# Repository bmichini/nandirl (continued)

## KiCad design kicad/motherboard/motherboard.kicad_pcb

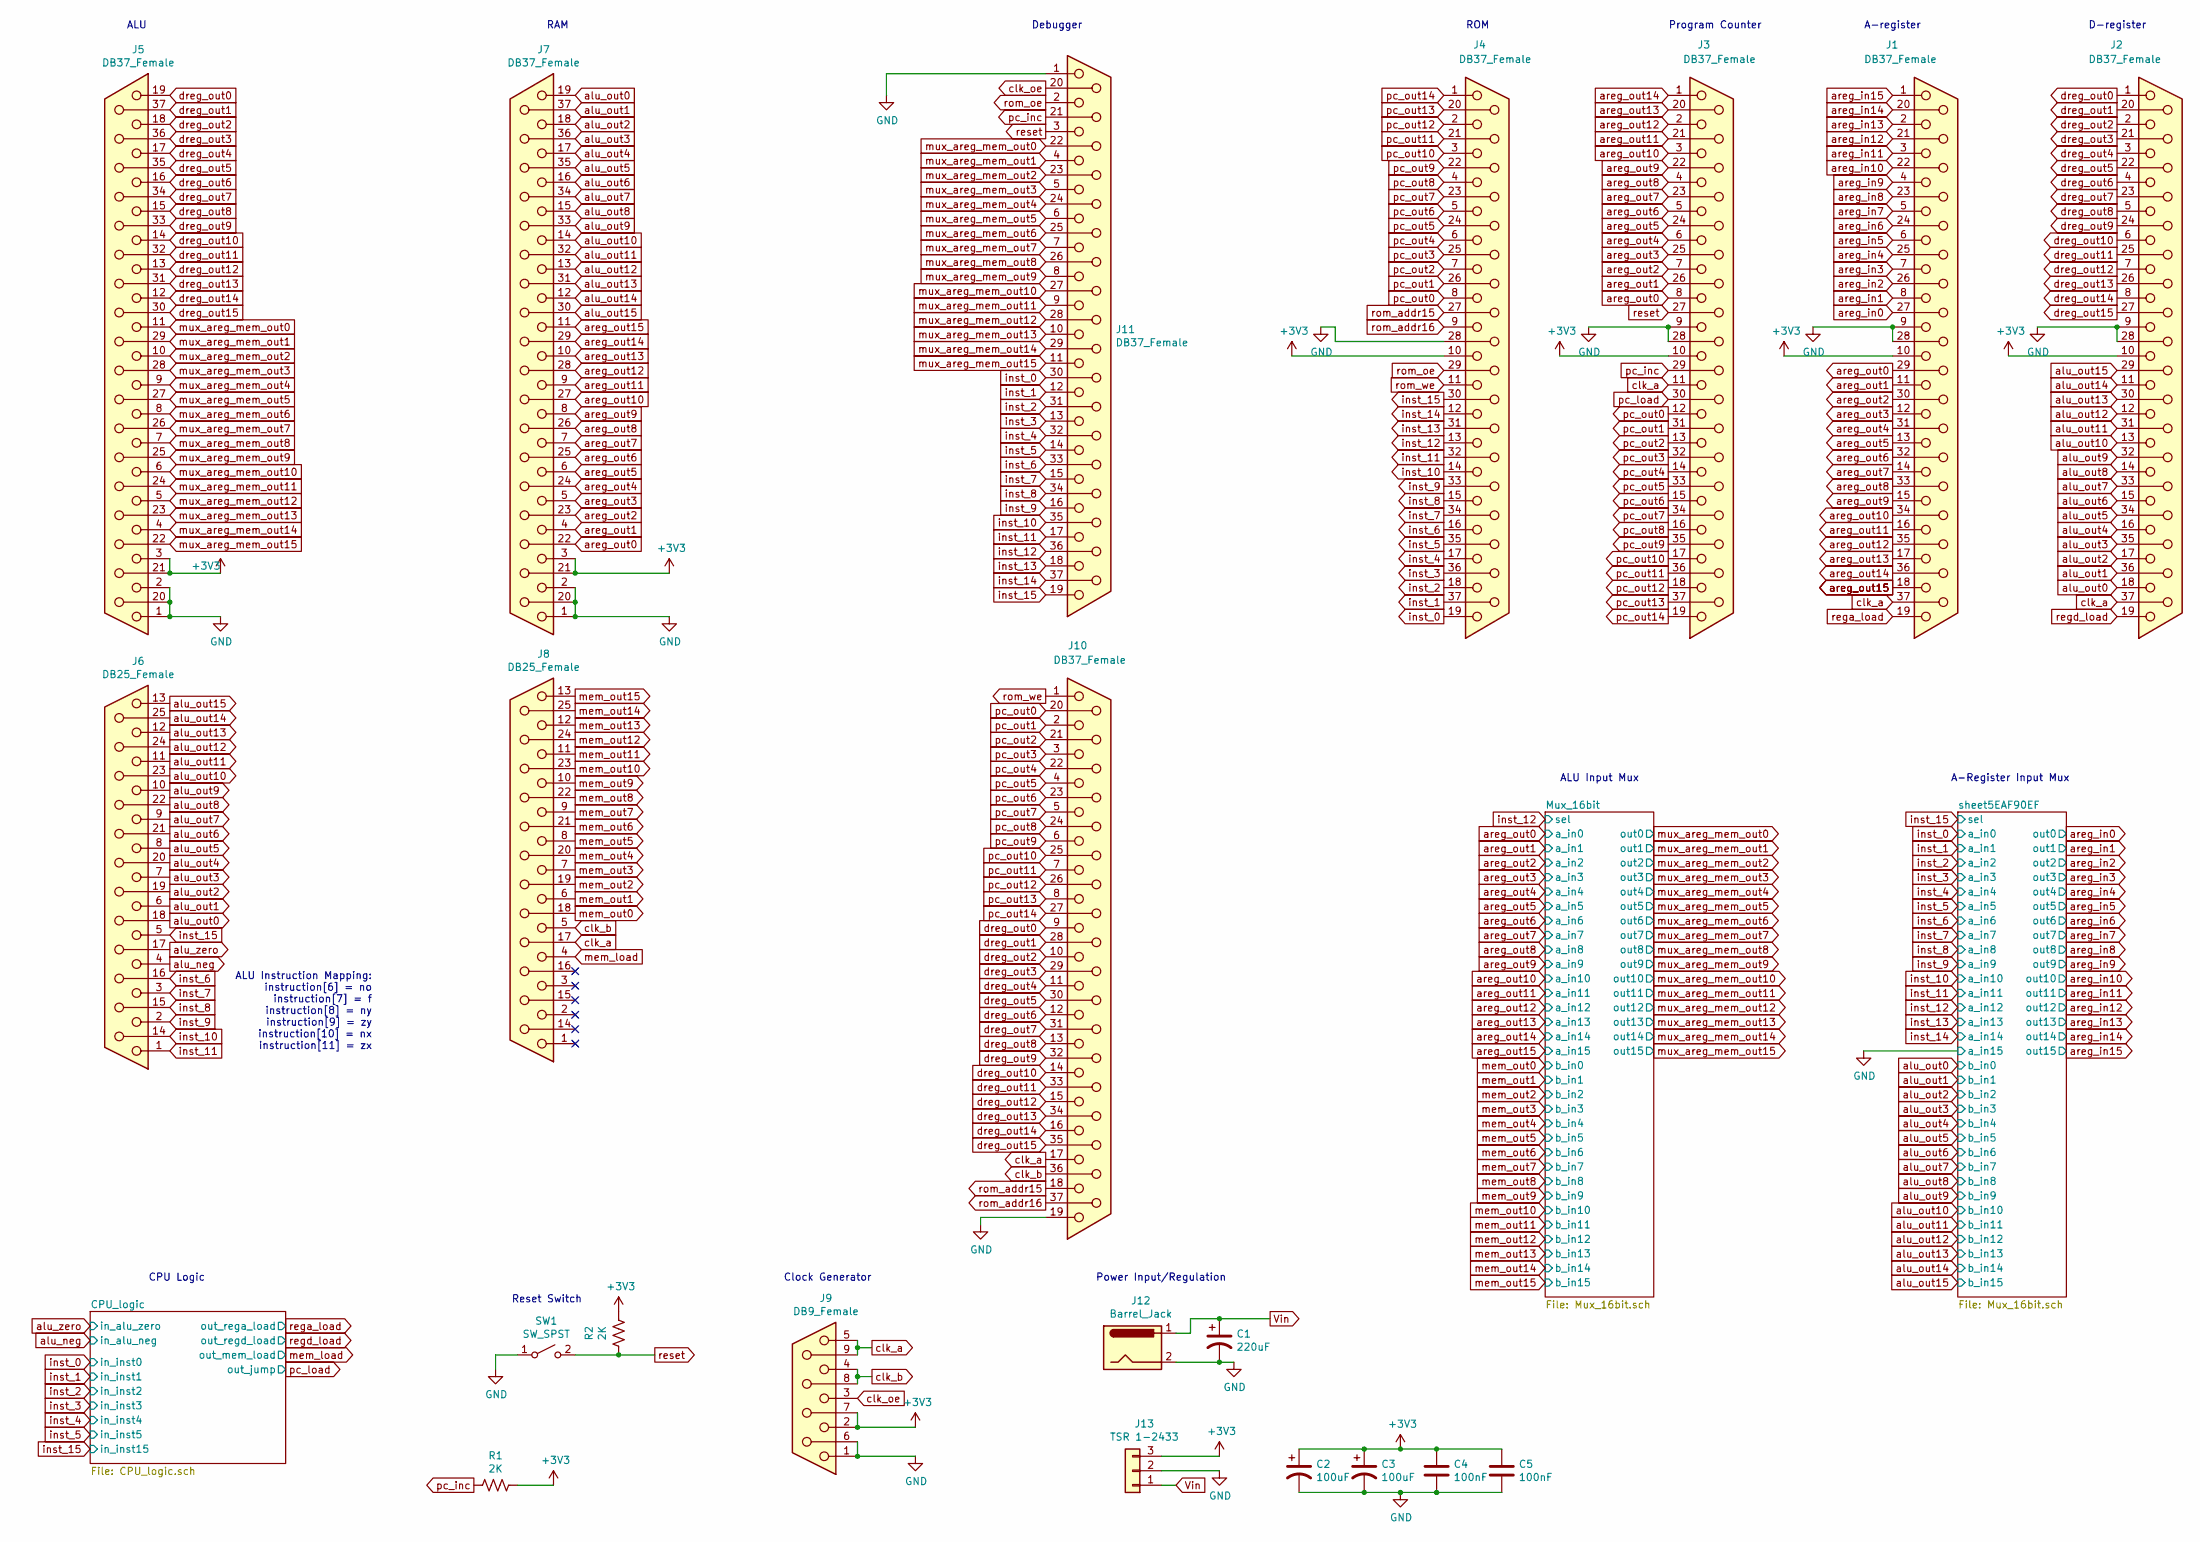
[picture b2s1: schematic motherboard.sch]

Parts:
C1: 220uF; CP_Radial_D10.0mm_P5.00mm; Digikey PN P5183-ND
C2, C3: 100uF; CP_Radial_D8.0mm_P2.50mm; Digikey PN P15797CT-ND
C4, C5: 100nF; C_Disc_D6.0mm_W2.5mm_P5.00mm; Digikey PN BC5229CT-ND
J1, J2, J3, J4, J5, J7, J10, J11: DB37_Female; DSUB-37_Female_Horizontal_P2.77x2.84mm_EdgePinOffset7.70mm_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; Digikey PN AE10941-ND
J6, J8: DB25_Female; DSUB-25_Female_Horizontal_P2.77x2.84mm_EdgePinOffset7.70mm_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; Digikey PN AE10935-ND
J9: DB9_Female; DSUB-9_Female_Horizontal_P2.77x2.84mm_EdgePinOffset7.70mm_H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; Digikey PN AE10921-ND
J12: Barrel_Jack; BarrelJack_CUI_PJ-063AH_Horizontal; Digikey PN CP-063AH-ND
J13: TSR 1-2433; PinHeader_1x03_P2.54mm_Vertical; Digikey PN 1951-2430-ND
R1, R2: 2K; R_1206_3216Metric; Digikey PN P2.0KECT-ND
SW1: SW_SPST; SW_SPST_B3S-1000; Digikey PN SW415-ND

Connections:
+3V3: C2.1, C3.1, C4.1, C5.1, J1.10, J2.10, J3.10, J4.10, J5.3, J5.21, J7.3, J7.21, J9.2, J9.7, J13.3, R1.1, R2.1; also elsewhere on the board
GND: C1.2, C2.2, C3.2, C4.2, C5.2, J1.9, J1.28, J2.9, J2.28, J3.9, J3.28, J4.28, J5.1, J5.2, J5.20, J7.1, J7.2, J7.20, J9.1, J9.6, J10.19, J11.1, J12.2, J13.2, SW1.1 (A); also elsewhere on the board
Vin: C1.1, J12.1, J13.1
alu_neg: J6.4; also elsewhere on the board
alu_out0: J2.18, J6.18, J7.19; also elsewhere on the board
alu_out1: J2.36, J6.6, J7.37; also elsewhere on the board
alu_out2: J2.17, J6.19, J7.18; also elsewhere on the board
alu_out3: J2.35, J6.7, J7.36; also elsewhere on the board
alu_out4: J2.16, J6.20, J7.17; also elsewhere on the board
alu_out5: J2.34, J6.8, J7.35; also elsewhere on the board
alu_out6: J2.15, J6.21, J7.16; also elsewhere on the board
alu_out7: J2.33, J6.9, J7.34; also elsewhere on the board
alu_out8: J2.14, J6.22, J7.15; also elsewhere on the board
alu_out9: J2.32, J6.10, J7.33; also elsewhere on the board
alu_out10: J2.13, J6.23, J7.14; also elsewhere on the board
alu_out11: J2.31, J6.11, J7.32; also elsewhere on the board
alu_out12: J2.12, J6.24, J7.13; also elsewhere on the board
alu_out13: J2.30, J6.12, J7.31; also elsewhere on the board
alu_out14: J2.11, J6.25, J7.12; also elsewhere on the board
alu_out15: J2.29, J6.13, J7.30; also elsewhere on the board
alu_zero: J6.17; also elsewhere on the board
areg_in0: J1.27; also elsewhere on the board
areg_in1: J1.8; also elsewhere on the board
areg_in2: J1.26; also elsewhere on the board
areg_in3: J1.7; also elsewhere on the board
areg_in4: J1.25; also elsewhere on the board
areg_in5: J1.6; also elsewhere on the board
areg_in6: J1.24; also elsewhere on the board
areg_in7: J1.5; also elsewhere on the board
areg_in8: J1.23; also elsewhere on the board
areg_in9: J1.4; also elsewhere on the board
areg_in10: J1.22; also elsewhere on the board
areg_in11: J1.3; also elsewhere on the board
areg_in12: J1.21; also elsewhere on the board
areg_in13: J1.2; also elsewhere on the board
areg_in14: J1.20; also elsewhere on the board
areg_in15: J1.1; also elsewhere on the board
areg_out0: J1.29, J3.8, J7.22; also elsewhere on the board
areg_out1: J1.11, J3.26, J7.4; also elsewhere on the board
areg_out2: J1.30, J3.7, J7.23; also elsewhere on the board
areg_out3: J1.12, J3.25, J7.5; also elsewhere on the board
areg_out4: J1.31, J3.6, J7.24; also elsewhere on the board
areg_out5: J1.13, J3.24, J7.6; also elsewhere on the board
areg_out6: J1.32, J3.5, J7.25; also elsewhere on the board
areg_out7: J1.14, J3.23, J7.7; also elsewhere on the board
areg_out8: J1.33, J3.4, J7.26; also elsewhere on the board
areg_out9: J1.15, J3.22, J7.8; also elsewhere on the board
areg_out10: J1.34, J3.3, J7.27; also elsewhere on the board
areg_out11: J1.16, J3.21, J7.9; also elsewhere on the board
areg_out12: J1.35, J3.2, J7.28; also elsewhere on the board
areg_out13: J1.17, J3.20, J7.10; also elsewhere on the board
areg_out14: J1.36, J3.1, J7.29; also elsewhere on the board
areg_out15: J1.18, J7.11; also elsewhere on the board
clk_a: J1.37, J2.37, J3.11, J8.17, J9.5, J9.9, J10.17
clk_b: J8.5, J9.4, J9.8, J10.36
clk_oe: J9.3, J11.20
dreg_out0: J2.1, J5.19, J10.9
dreg_out1: J2.20, J5.37, J10.28
dreg_out2: J2.2, J5.18, J10.10
dreg_out3: J2.21, J5.36, J10.29
dreg_out4: J2.3, J5.17, J10.11
dreg_out5: J2.22, J5.35, J10.30
dreg_out6: J2.4, J5.16, J10.12
dreg_out7: J2.23, J5.34, J10.31
dreg_out8: J2.5, J5.15, J10.13
dreg_out9: J2.24, J5.33, J10.32
dreg_out10: J2.6, J5.14, J10.14
dreg_out11: J2.25, J5.32, J10.33
dreg_out12: J2.7, J5.13, J10.15
dreg_out13: J2.26, J5.31, J10.34
dreg_out14: J2.8, J5.12, J10.16
dreg_out15: J2.27, J5.30, J10.35
inst_0: J4.19, J11.30; also elsewhere on the board
inst_1: J4.37, J11.12; also elsewhere on the board
inst_2: J4.18, J11.31; also elsewhere on the board
inst_3: J4.36, J11.13; also elsewhere on the board
inst_4: J4.17, J11.32; also elsewhere on the board
inst_5: J4.35, J11.14; also elsewhere on the board
inst_6: J4.16, J6.16, J11.33; also elsewhere on the board
inst_7: J4.34, J6.3, J11.15; also elsewhere on the board
inst_8: J4.15, J6.15, J11.34; also elsewhere on the board
inst_9: J4.33, J6.2, J11.16; also elsewhere on the board
inst_10: J4.14, J6.14, J11.35; also elsewhere on the board
inst_11: J4.32, J6.1, J11.17; also elsewhere on the board
inst_12: J4.13, J11.36; also elsewhere on the board
inst_13: J4.31, J11.18; also elsewhere on the board
inst_14: J4.12, J11.37; also elsewhere on the board
inst_15: J4.30, J6.5, J11.19; also elsewhere on the board
mem_load: J8.4; also elsewhere on the board
mem_out0: J8.18; also elsewhere on the board
mem_out1: J8.6; also elsewhere on the board
mem_out2: J8.19; also elsewhere on the board
mem_out3: J8.7; also elsewhere on the board
mem_out4: J8.20; also elsewhere on the board
mem_out5: J8.8; also elsewhere on the board
mem_out6: J8.21; also elsewhere on the board
mem_out7: J8.9; also elsewhere on the board
mem_out8: J8.22; also elsewhere on the board
mem_out9: J8.10; also elsewhere on the board
mem_out10: J8.23; also elsewhere on the board
mem_out11: J8.11; also elsewhere on the board
mem_out12: J8.24; also elsewhere on the board
mem_out13: J8.12; also elsewhere on the board
mem_out14: J8.25; also elsewhere on the board
mem_out15: J8.13; also elsewhere on the board
mux_areg_mem_out0: J5.11, J11.22; also elsewhere on the board
mux_areg_mem_out1: J5.29, J11.4; also elsewhere on the board
mux_areg_mem_out2: J5.10, J11.23; also elsewhere on the board
mux_areg_mem_out3: J5.28, J11.5; also elsewhere on the board
mux_areg_mem_out4: J5.9, J11.24; also elsewhere on the board
mux_areg_mem_out5: J5.27, J11.6; also elsewhere on the board
mux_areg_mem_out6: J5.8, J11.25; also elsewhere on the board
mux_areg_mem_out7: J5.26, J11.7; also elsewhere on the board
mux_areg_mem_out8: J5.7, J11.26; also elsewhere on the board
mux_areg_mem_out9: J5.25, J11.8; also elsewhere on the board
mux_areg_mem_out10: J5.6, J11.27; also elsewhere on the board
mux_areg_mem_out11: J5.24, J11.9; also elsewhere on the board
mux_areg_mem_out12: J5.5, J11.28; also elsewhere on the board
mux_areg_mem_out13: J5.23, J11.10; also elsewhere on the board
mux_areg_mem_out14: J5.4, J11.29; also elsewhere on the board
mux_areg_mem_out15: J5.22, J11.11; also elsewhere on the board
pc_inc: J3.29, J11.21, R1.2
pc_load: J3.30; also elsewhere on the board
pc_out0: J3.12, J4.8, J10.20
pc_out1: J3.31, J4.26, J10.2
pc_out2: J3.13, J4.7, J10.21
pc_out3: J3.32, J4.25, J10.3
pc_out4: J3.14, J4.6, J10.22
pc_out5: J3.33, J4.24, J10.4
pc_out6: J3.15, J4.5, J10.23
pc_out7: J3.34, J4.23, J10.5
pc_out8: J3.16, J4.4, J10.24
pc_out9: J3.35, J4.22, J10.6
pc_out10: J3.17, J4.3, J10.25
pc_out11: J3.36, J4.21, J10.7
pc_out12: J3.18, J4.2, J10.26
pc_out13: J3.37, J4.20, J10.8
pc_out14: J3.19, J4.1, J10.27
rega_load: J1.19; also elsewhere on the board
regd_load: J2.19; also elsewhere on the board
reset: J3.27, J11.3, R2.2, SW1.2 (B)
rom_addr15: J4.27, J10.18
rom_addr16: J4.9, J10.37
rom_oe: J4.29, J11.2
rom_we: J4.11, J10.1

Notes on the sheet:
D-register
A-register
Program Counter
ROM
ALU
ALU Instruction Mapping: instruction[6] = no instruction[7] = f instruction[8] = ny instruction[9] = zy instruction[10] = nx instruction[11] = zx
RAM
ALU Input Mux
A-Register Input Mux
Clock Generator
CPU Logic
Debugger
Power Input/Regulation
Reset Switch

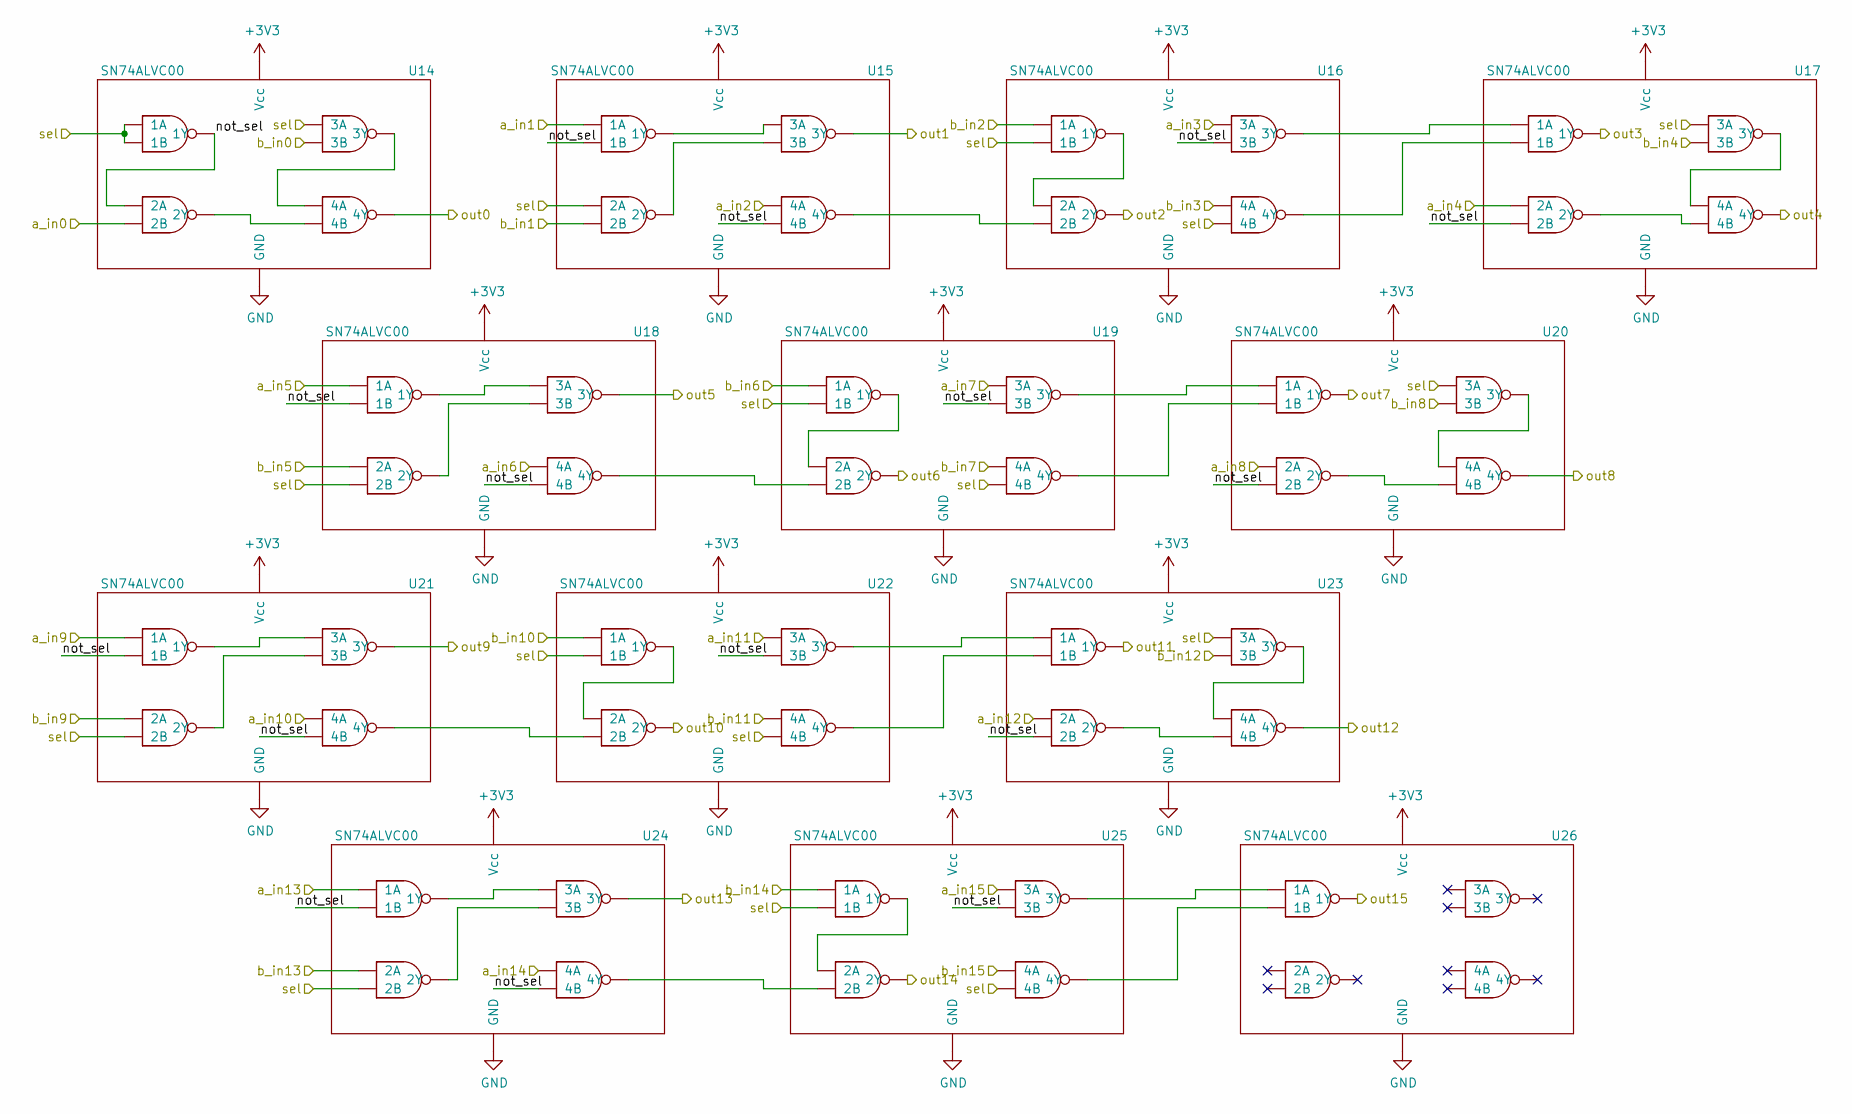
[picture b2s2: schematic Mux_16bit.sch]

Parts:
U1, U2, U3, U4, U5, U6, U7, U8, U9, U10, U11, U12, U13: SN74ALVC00; TSSOP-14_4.4x5mm_P0.65mm; Digikey PN 296-5104-1-ND

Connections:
+3V3: U1.14 (Vcc), U2.14 (Vcc), U3.14 (Vcc), U4.14 (Vcc), U5.14 (Vcc), U6.14 (Vcc), U7.14 (Vcc), U8.14 (Vcc), U9.14 (Vcc), U10.14 (Vcc), U11.14 (Vcc), U12.14 (Vcc), U13.14 (Vcc); also elsewhere on the board
/Mux_16bit/not_sel: U1.3 (1Y), U1.4 (2A), U2.2 (1B), U2.13 (4B), U3.10 (3B), U4.5 (2B), U5.2 (1B), U5.13 (4B), U6.10 (3B), U7.5 (2B), U8.2 (1B), U8.13 (4B), U9.10 (3B), U10.5 (2B), U11.2 (1B), U11.13 (4B), U12.10 (3B)
GND: U1.7 (GND), U2.7 (GND), U3.7 (GND), U4.7 (GND), U5.7 (GND), U6.7 (GND), U7.7 (GND), U8.7 (GND), U9.7 (GND), U10.7 (GND), U11.7 (GND), U12.7 (GND), U13.7 (GND); also elsewhere on the board
unnamed: U1.8 (3Y), U1.12 (4A)
unnamed: U1.6 (2Y), U1.13 (4B)
unnamed: U2.3 (1Y), U2.9 (3A)
unnamed: U2.6 (2Y), U2.10 (3B)
unnamed: U2.11 (4Y), U3.5 (2B)
unnamed: U3.3 (1Y), U3.4 (2A)
unnamed: U3.8 (3Y), U4.1 (1A)
unnamed: U3.11 (4Y), U4.2 (1B)
unnamed: U4.8 (3Y), U4.12 (4A)
unnamed: U4.6 (2Y), U4.13 (4B)
unnamed: U5.3 (1Y), U5.9 (3A)
unnamed: U5.6 (2Y), U5.10 (3B)
unnamed: U5.11 (4Y), U6.5 (2B)
unnamed: U6.3 (1Y), U6.4 (2A)
unnamed: U6.8 (3Y), U7.1 (1A)
unnamed: U6.11 (4Y), U7.2 (1B)
unnamed: U7.8 (3Y), U7.12 (4A)
unnamed: U7.6 (2Y), U7.13 (4B)
unnamed: U8.3 (1Y), U8.9 (3A)
unnamed: U8.6 (2Y), U8.10 (3B)
unnamed: U8.11 (4Y), U9.5 (2B)
unnamed: U9.3 (1Y), U9.4 (2A)
unnamed: U9.8 (3Y), U10.1 (1A)
unnamed: U9.11 (4Y), U10.2 (1B)
unnamed: U10.8 (3Y), U10.12 (4A)
unnamed: U10.6 (2Y), U10.13 (4B)
unnamed: U11.3 (1Y), U11.9 (3A)
unnamed: U11.6 (2Y), U11.10 (3B)
unnamed: U11.11 (4Y), U12.5 (2B)
unnamed: U12.3 (1Y), U12.4 (2A)
unnamed: U12.8 (3Y), U13.1 (1A)
unnamed: U12.11 (4Y), U13.2 (1B)
areg_out0: U1.5 (2B); also elsewhere on the board
areg_out1: U2.1 (1A); also elsewhere on the board
areg_out2: U2.12 (4A); also elsewhere on the board
areg_out3: U3.9 (3A); also elsewhere on the board
areg_out4: U4.4 (2A); also elsewhere on the board
areg_out5: U5.1 (1A); also elsewhere on the board
areg_out6: U5.12 (4A); also elsewhere on the board
areg_out7: U6.9 (3A); also elsewhere on the board
areg_out8: U7.4 (2A); also elsewhere on the board
areg_out9: U8.1 (1A); also elsewhere on the board
areg_out10: U8.12 (4A); also elsewhere on the board
areg_out11: U9.9 (3A); also elsewhere on the board
areg_out12: U10.4 (2A); also elsewhere on the board
areg_out13: U11.1 (1A); also elsewhere on the board
areg_out14: U11.12 (4A); also elsewhere on the board
areg_out15: U12.9 (3A); also elsewhere on the board
inst_12: U1.1 (1A), U1.2 (1B), U1.9 (3A), U2.4 (2A), U3.2 (1B), U3.13 (4B), U4.9 (3A), U5.5 (2B), U6.2 (1B), U6.13 (4B), U7.9 (3A), U8.5 (2B), U9.2 (1B), U9.13 (4B), U10.9 (3A), U11.5 (2B), U12.2 (1B), U12.13 (4B); also elsewhere on the board
mem_out0: U1.10 (3B); also elsewhere on the board
mem_out1: U2.5 (2B); also elsewhere on the board
mem_out2: U3.1 (1A); also elsewhere on the board
mem_out3: U3.12 (4A); also elsewhere on the board
mem_out4: U4.10 (3B); also elsewhere on the board
mem_out5: U5.4 (2A); also elsewhere on the board
mem_out6: U6.1 (1A); also elsewhere on the board
mem_out7: U6.12 (4A); also elsewhere on the board
mem_out8: U7.10 (3B); also elsewhere on the board
mem_out9: U8.4 (2A); also elsewhere on the board
mem_out10: U9.1 (1A); also elsewhere on the board
mem_out11: U9.12 (4A); also elsewhere on the board
mem_out12: U10.10 (3B); also elsewhere on the board
mem_out13: U11.4 (2A); also elsewhere on the board
mem_out14: U12.1 (1A); also elsewhere on the board
mem_out15: U12.12 (4A); also elsewhere on the board
mux_areg_mem_out0: U1.11 (4Y); also elsewhere on the board
mux_areg_mem_out1: U2.8 (3Y); also elsewhere on the board
mux_areg_mem_out2: U3.6 (2Y); also elsewhere on the board
mux_areg_mem_out3: U4.3 (1Y); also elsewhere on the board
mux_areg_mem_out4: U4.11 (4Y); also elsewhere on the board
mux_areg_mem_out5: U5.8 (3Y); also elsewhere on the board
mux_areg_mem_out6: U6.6 (2Y); also elsewhere on the board
mux_areg_mem_out7: U7.3 (1Y); also elsewhere on the board
mux_areg_mem_out8: U7.11 (4Y); also elsewhere on the board
mux_areg_mem_out9: U8.8 (3Y); also elsewhere on the board
mux_areg_mem_out10: U9.6 (2Y); also elsewhere on the board
mux_areg_mem_out11: U10.3 (1Y); also elsewhere on the board
mux_areg_mem_out12: U10.11 (4Y); also elsewhere on the board
mux_areg_mem_out13: U11.8 (3Y); also elsewhere on the board
mux_areg_mem_out14: U12.6 (2Y); also elsewhere on the board
mux_areg_mem_out15: U13.3 (1Y); also elsewhere on the board

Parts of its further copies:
U14, U15, U16, U17, U18, U19, U20, U21, U22, U23, U24, U25, U26: SN74ALVC00; TSSOP-14_4.4x5mm_P0.65mm; Digikey PN 296-5104-1-ND

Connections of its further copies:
+3V3: U14.14 (Vcc), U15.14 (Vcc), U16.14 (Vcc), U17.14 (Vcc), U18.14 (Vcc), U19.14 (Vcc), U20.14 (Vcc), U21.14 (Vcc), U22.14 (Vcc), U23.14 (Vcc), U24.14 (Vcc), U25.14 (Vcc), U26.14 (Vcc); also elsewhere on the board
/sheet5EAF90EF/not_sel: U14.3 (1Y), U14.4 (2A), U15.2 (1B), U15.13 (4B), U16.10 (3B), U17.5 (2B), U18.2 (1B), U18.13 (4B), U19.10 (3B), U20.5 (2B), U21.2 (1B), U21.13 (4B), U22.10 (3B), U23.5 (2B), U24.2 (1B), U24.13 (4B), U25.10 (3B)
GND: U14.7 (GND), U15.7 (GND), U16.7 (GND), U17.7 (GND), U18.7 (GND), U19.7 (GND), U20.7 (GND), U21.7 (GND), U22.7 (GND), U23.7 (GND), U24.7 (GND), U25.7 (GND), U25.9 (3A), U26.7 (GND); also elsewhere on the board
unnamed: U14.8 (3Y), U14.12 (4A)
unnamed: U14.6 (2Y), U14.13 (4B)
unnamed: U15.3 (1Y), U15.9 (3A)
unnamed: U15.6 (2Y), U15.10 (3B)
unnamed: U15.11 (4Y), U16.5 (2B)
unnamed: U16.3 (1Y), U16.4 (2A)
unnamed: U16.8 (3Y), U17.1 (1A)
unnamed: U16.11 (4Y), U17.2 (1B)
unnamed: U17.8 (3Y), U17.12 (4A)
unnamed: U17.6 (2Y), U17.13 (4B)
unnamed: U18.3 (1Y), U18.9 (3A)
unnamed: U18.6 (2Y), U18.10 (3B)
unnamed: U18.11 (4Y), U19.5 (2B)
unnamed: U19.3 (1Y), U19.4 (2A)
unnamed: U19.8 (3Y), U20.1 (1A)
unnamed: U19.11 (4Y), U20.2 (1B)
unnamed: U20.8 (3Y), U20.12 (4A)
unnamed: U20.6 (2Y), U20.13 (4B)
unnamed: U21.3 (1Y), U21.9 (3A)
unnamed: U21.6 (2Y), U21.10 (3B)
unnamed: U21.11 (4Y), U22.5 (2B)
unnamed: U22.3 (1Y), U22.4 (2A)
unnamed: U22.8 (3Y), U23.1 (1A)
unnamed: U22.11 (4Y), U23.2 (1B)
unnamed: U23.8 (3Y), U23.12 (4A)
unnamed: U23.6 (2Y), U23.13 (4B)
unnamed: U24.3 (1Y), U24.9 (3A)
unnamed: U24.6 (2Y), U24.10 (3B)
unnamed: U24.11 (4Y), U25.5 (2B)
unnamed: U25.3 (1Y), U25.4 (2A)
unnamed: U25.8 (3Y), U26.1 (1A)
unnamed: U25.11 (4Y), U26.2 (1B)
alu_out0: U14.10 (3B); also elsewhere on the board
alu_out1: U15.5 (2B); also elsewhere on the board
alu_out2: U16.1 (1A); also elsewhere on the board
alu_out3: U16.12 (4A); also elsewhere on the board
alu_out4: U17.10 (3B); also elsewhere on the board
alu_out5: U18.4 (2A); also elsewhere on the board
alu_out6: U19.1 (1A); also elsewhere on the board
alu_out7: U19.12 (4A); also elsewhere on the board
alu_out8: U20.10 (3B); also elsewhere on the board
alu_out9: U21.4 (2A); also elsewhere on the board
alu_out10: U22.1 (1A); also elsewhere on the board
alu_out11: U22.12 (4A); also elsewhere on the board
alu_out12: U23.10 (3B); also elsewhere on the board
alu_out13: U24.4 (2A); also elsewhere on the board
alu_out14: U25.1 (1A); also elsewhere on the board
alu_out15: U25.12 (4A); also elsewhere on the board
areg_in0: U14.11 (4Y); also elsewhere on the board
areg_in1: U15.8 (3Y); also elsewhere on the board
areg_in2: U16.6 (2Y); also elsewhere on the board
areg_in3: U17.3 (1Y); also elsewhere on the board
areg_in4: U17.11 (4Y); also elsewhere on the board
areg_in5: U18.8 (3Y); also elsewhere on the board
areg_in6: U19.6 (2Y); also elsewhere on the board
areg_in7: U20.3 (1Y); also elsewhere on the board
areg_in8: U20.11 (4Y); also elsewhere on the board
areg_in9: U21.8 (3Y); also elsewhere on the board
areg_in10: U22.6 (2Y); also elsewhere on the board
areg_in11: U23.3 (1Y); also elsewhere on the board
areg_in12: U23.11 (4Y); also elsewhere on the board
areg_in13: U24.8 (3Y); also elsewhere on the board
areg_in14: U25.6 (2Y); also elsewhere on the board
areg_in15: U26.3 (1Y); also elsewhere on the board
inst_0: U14.5 (2B); also elsewhere on the board
inst_1: U15.1 (1A); also elsewhere on the board
inst_2: U15.12 (4A); also elsewhere on the board
inst_3: U16.9 (3A); also elsewhere on the board
inst_4: U17.4 (2A); also elsewhere on the board
inst_5: U18.1 (1A); also elsewhere on the board
inst_6: U18.12 (4A); also elsewhere on the board
inst_7: U19.9 (3A); also elsewhere on the board
inst_8: U20.4 (2A); also elsewhere on the board
inst_9: U21.1 (1A); also elsewhere on the board
inst_10: U21.12 (4A); also elsewhere on the board
inst_11: U22.9 (3A); also elsewhere on the board
inst_12: U23.4 (2A); also elsewhere on the board
inst_13: U24.1 (1A); also elsewhere on the board
inst_14: U24.12 (4A); also elsewhere on the board
inst_15: U14.1 (1A), U14.2 (1B), U14.9 (3A), U15.4 (2A), U16.2 (1B), U16.13 (4B), U17.9 (3A), U18.5 (2B), U19.2 (1B), U19.13 (4B), U20.9 (3A), U21.5 (2B), U22.2 (1B), U22.13 (4B), U23.9 (3A), U24.5 (2B), U25.2 (1B), U25.13 (4B); also elsewhere on the board

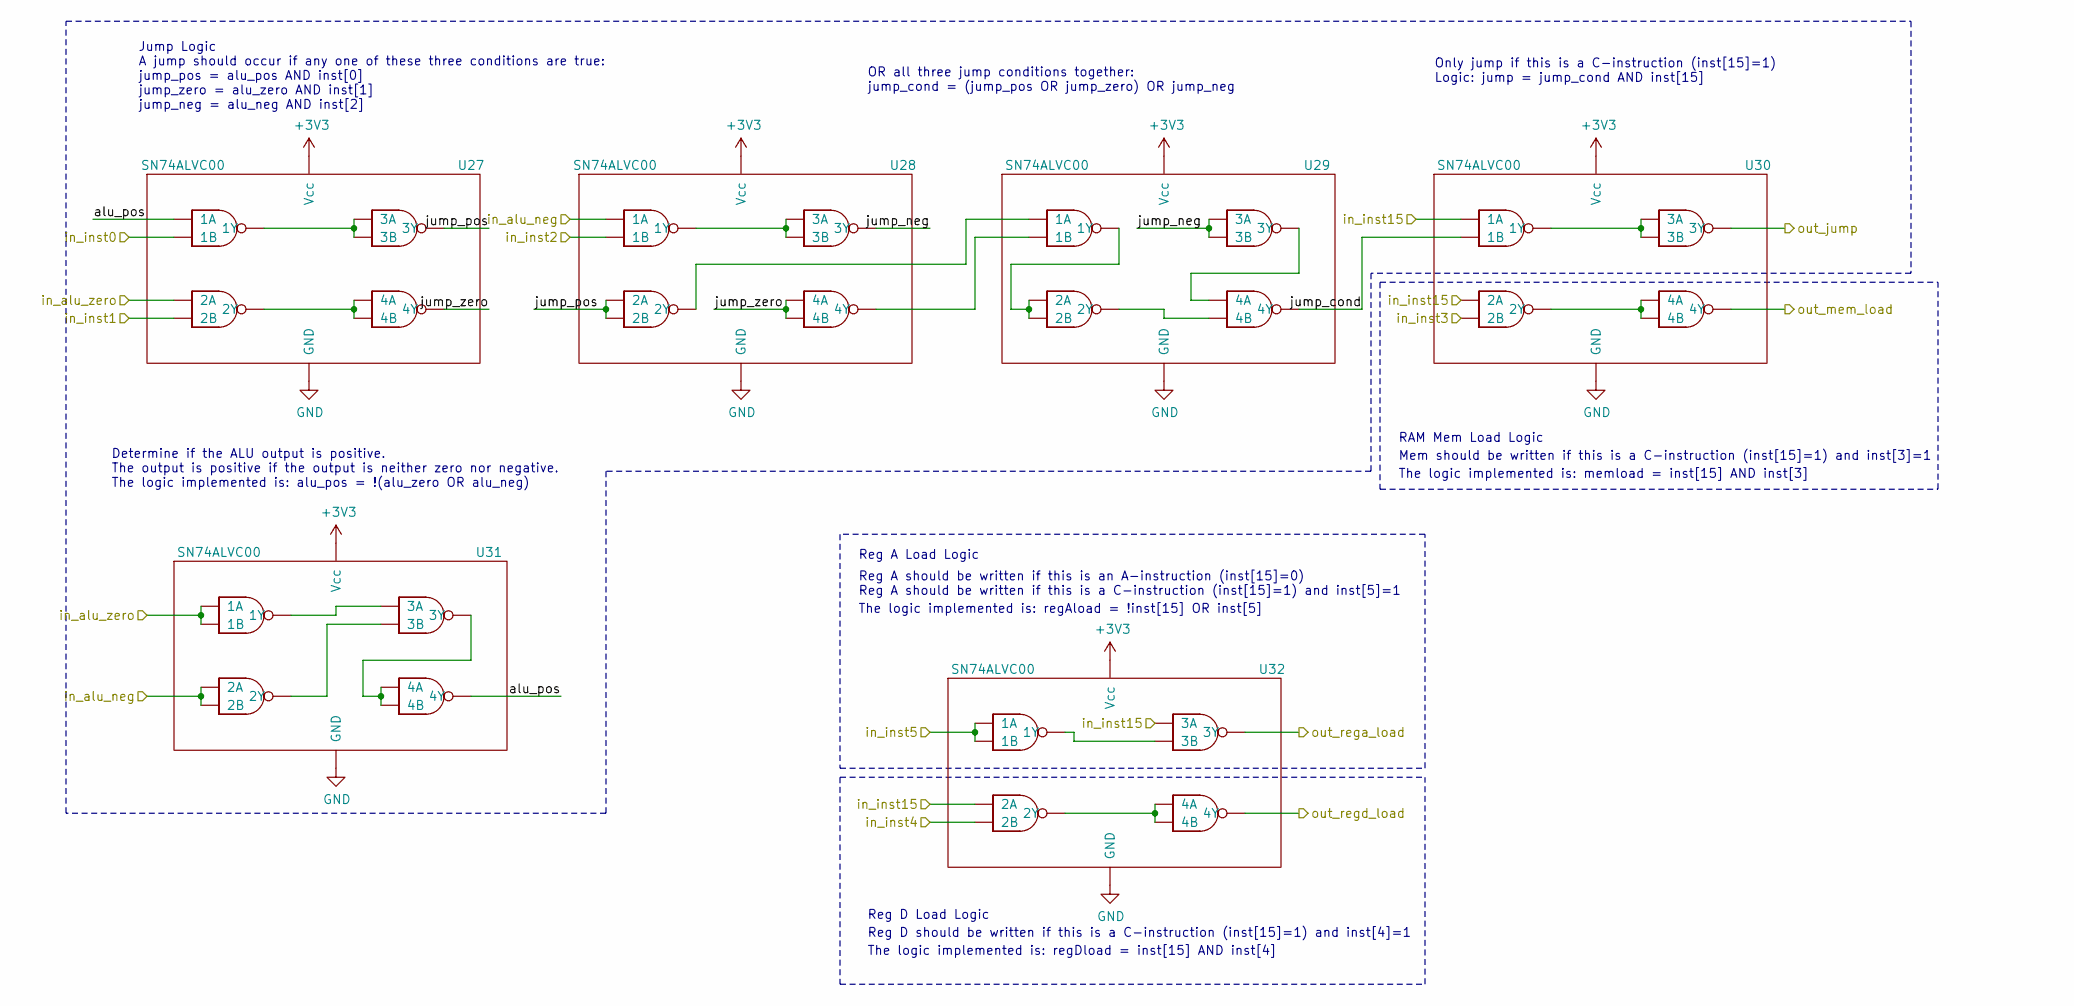
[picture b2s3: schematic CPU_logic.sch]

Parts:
U27, U28, U29, U30, U31, U32: SN74ALVC00; TSSOP-14_4.4x5mm_P0.65mm; Digikey PN 296-5104-1-ND

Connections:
+3V3: U27.14 (Vcc), U28.14 (Vcc), U29.14 (Vcc), U30.14 (Vcc), U31.14 (Vcc), U32.14 (Vcc); also elsewhere on the board
/CPU_logic/alu_pos: U27.1 (1A), U31.11 (4Y)
/CPU_logic/jump_cond: U29.11 (4Y), U30.2 (1B)
/CPU_logic/jump_neg: U28.8 (3Y), U29.9 (3A), U29.10 (3B)
/CPU_logic/jump_pos: U27.8 (3Y), U28.4 (2A), U28.5 (2B)
/CPU_logic/jump_zero: U27.11 (4Y), U28.12 (4A), U28.13 (4B)
GND: U27.7 (GND), U28.7 (GND), U29.7 (GND), U30.7 (GND), U31.7 (GND), U32.7 (GND); also elsewhere on the board
unnamed: U27.3 (1Y), U27.9 (3A), U27.10 (3B)
unnamed: U27.6 (2Y), U27.12 (4A), U27.13 (4B)
unnamed: U28.6 (2Y), U29.1 (1A)
unnamed: U28.3 (1Y), U28.9 (3A), U28.10 (3B)
unnamed: U28.11 (4Y), U29.2 (1B)
unnamed: U29.3 (1Y), U29.4 (2A), U29.5 (2B)
unnamed: U29.8 (3Y), U29.12 (4A)
unnamed: U29.6 (2Y), U29.13 (4B)
unnamed: U30.3 (1Y), U30.9 (3A), U30.10 (3B)
unnamed: U30.6 (2Y), U30.12 (4A), U30.13 (4B)
unnamed: U31.3 (1Y), U31.9 (3A)
unnamed: U31.6 (2Y), U31.10 (3B)
unnamed: U31.8 (3Y), U31.12 (4A), U31.13 (4B)
unnamed: U32.3 (1Y), U32.10 (3B)
unnamed: U32.6 (2Y), U32.12 (4A), U32.13 (4B)
alu_neg: U28.1 (1A), U31.4 (2A), U31.5 (2B); also elsewhere on the board
alu_zero: U27.4 (2A), U31.1 (1A), U31.2 (1B); also elsewhere on the board
inst_0: U27.2 (1B); also elsewhere on the board
inst_1: U27.5 (2B); also elsewhere on the board
inst_2: U28.2 (1B); also elsewhere on the board
inst_3: U30.5 (2B); also elsewhere on the board
inst_4: U32.5 (2B); also elsewhere on the board
inst_5: U32.1 (1A), U32.2 (1B); also elsewhere on the board
inst_15: U30.1 (1A), U30.4 (2A), U32.4 (2A), U32.9 (3A); also elsewhere on the board
mem_load: U30.11 (4Y); also elsewhere on the board
pc_load: U30.8 (3Y); also elsewhere on the board
rega_load: U32.8 (3Y); also elsewhere on the board
regd_load: U32.11 (4Y); also elsewhere on the board

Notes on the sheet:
Reg A Load Logic
Reg A should be written if this is an A-instruction (inst[15]=0) Reg A should be written if this is a C-instruction (inst[15]=1) and inst[5]=1
The logic implemented is: regAload = !inst[15] OR inst[5]
Reg D Load Logic
The logic implemented is: regDload = inst[15] AND inst[4]
Reg D should be written if this is a C-instruction (inst[15]=1) and inst[4]=1
Determine if the ALU output is positive. The output is positive if the output is neither zero nor negative. The logic implemented is: alu_pos = !(alu_zero OR alu_neg)
Jump Logic A jump should occur if any one of these three conditions are true: jump_pos = alu_pos AND inst[0] jump_zero = alu_zero AND inst[1] jump_neg = alu_neg AND inst[2]
OR all three jump conditions together: jump_cond = (jump_pos OR jump_zero) OR jump_neg
Only jump if this is a C-instruction (inst[15]=1) Logic: jump = jump_cond AND inst[15]
RAM Mem Load Logic
The logic implemented is: memload = inst[15] AND inst[3]
Mem should be written if this is a C-instruction (inst[15]=1) and inst[3]=1

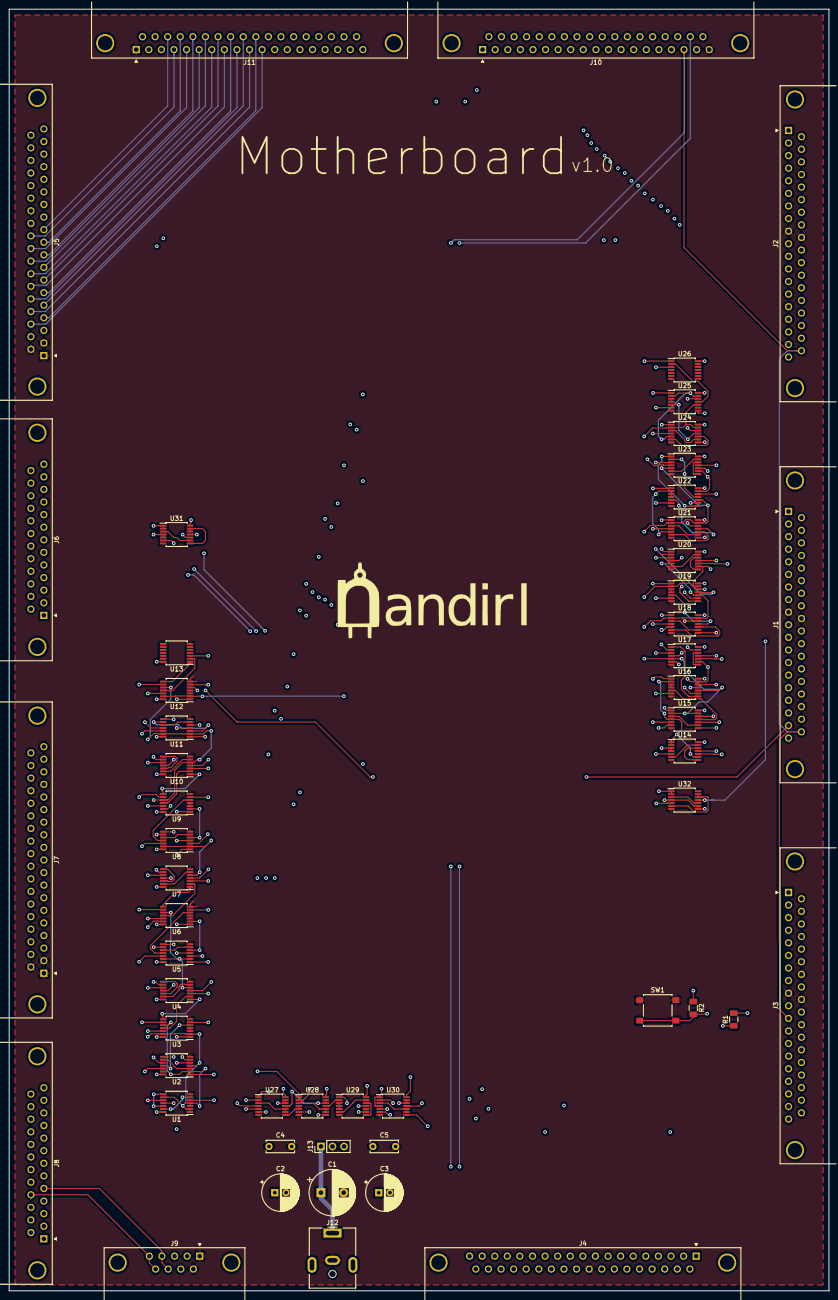
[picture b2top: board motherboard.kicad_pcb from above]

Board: 4 copper layers, 180.3 x 281.9 mm, 53 parts (0 on the bottom side), 231 nets.
